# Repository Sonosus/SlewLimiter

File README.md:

# Slew Limiter
A Kosmo format slew limiter. Not tested, but it is very simple and probably works.
No panel is provided - I use custom wooden panels. I can design one though, if folks want. Send me an email or make an issue if you do.

# Attribution
This is a dual PCB of the circuit [here](http://synovatron.blogspot.com/p/diy-ideas.html). All credit to the original author.

[![CC BY-SA 4.0][cc-by-sa-shield]][cc-by-sa]

This work is licensed under a
[Creative Commons Attribution-ShareAlike 4.0 International License][cc-by-sa].

[![CC BY-SA 4.0][cc-by-sa-image]][cc-by-sa]

[cc-by-sa]: http://creativecommons.org/licenses/by-sa/4.0/
[cc-by-sa-image]: https://licensebuttons.net/l/by-sa/4.0/88x31.png
[cc-by-sa-shield]: https://img.shields.io/badge/License-CC%20BY--SA%204.0-lightgrey.svg

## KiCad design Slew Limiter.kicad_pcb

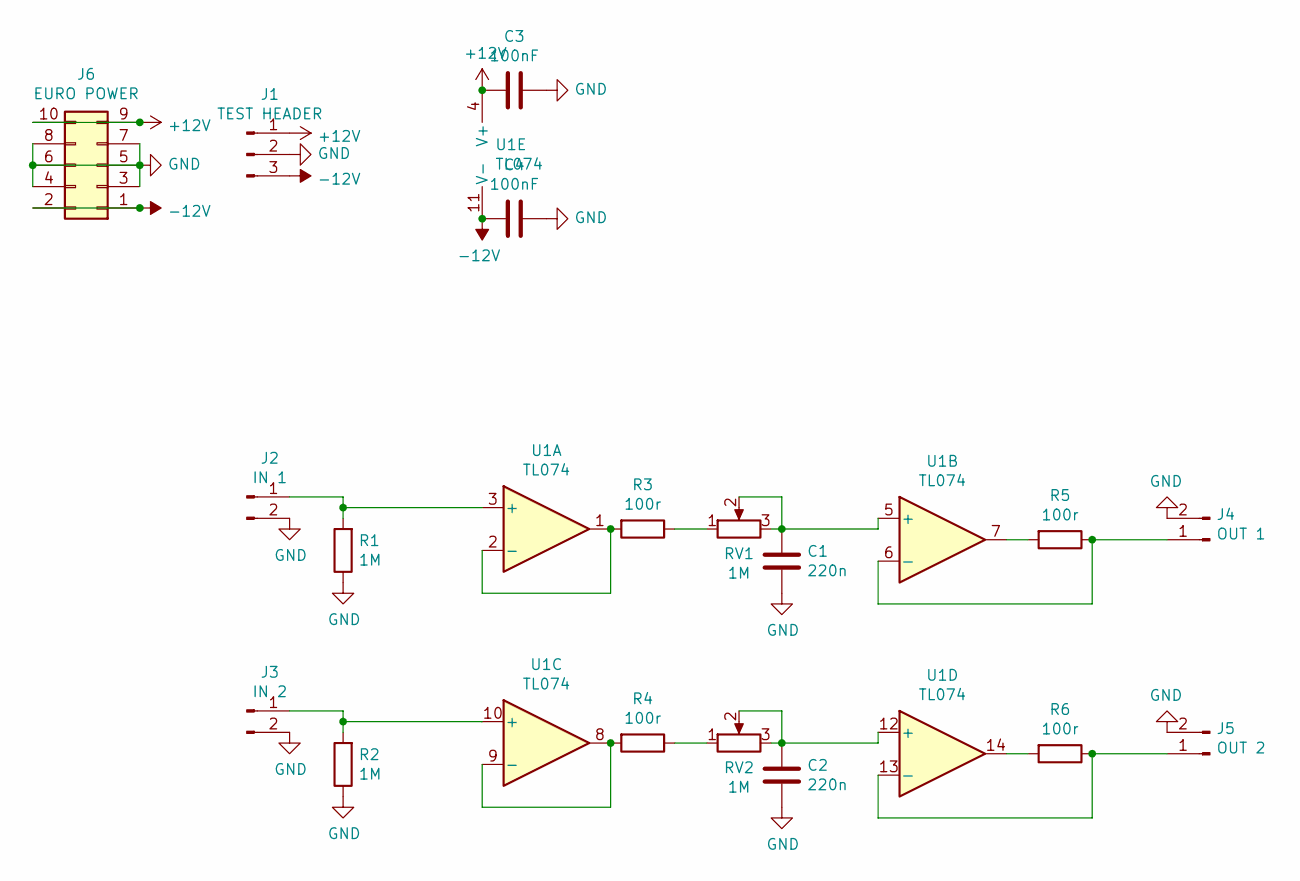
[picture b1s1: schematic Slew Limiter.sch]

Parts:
C1, C2: 220n; C_Disc_D4.3mm_W1.9mm_P5.00mm
C3, C4: 100nF; C_Disc_D6.0mm_W4.4mm_P5.00mm
J1: TEST HEADER; PinHeader_1x03_P2.54mm_Vertical
J2: IN 1; PinHeader_1x02_P2.54mm_Vertical
J3: IN 2; PinHeader_1x02_P2.54mm_Vertical
J4: OUT 1; PinHeader_1x02_P2.54mm_Vertical
J5: OUT 2; PinHeader_1x02_P2.54mm_Vertical
J6: EURO POWER; PinHeader_2x05_P2.54mm_Vertical
R1, R2: 1M; R_Axial_DIN0207_L6.3mm_D2.5mm_P7.62mm_Horizontal
R3, R4, R5, R6: 100r; R_Axial_DIN0207_L6.3mm_D2.5mm_P7.62mm_Horizontal
RV1, RV2: 1M; Alpha_16mm_PCBMount
U1: TL074; DIP-14_W7.62mm_Socket_LongPads

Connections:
+12V: C3.2, J1.1, J6.9, J6.10, U1.4 (V+)
-12V: C4.2, J1.3, J6.1, J6.2, U1.11 (V-)
GND: C1.2, C2.2, C3.1, C4.1, J1.2, J2.2, J3.2, J4.2, J5.2, J6.3, J6.4, J6.5, J6.6, J6.7, J6.8, R1.1, R2.1
unnamed: C1.1, RV1.2, RV1.3, U1.5 (+)
unnamed: C2.1, RV2.2, RV2.3, U1.12 (+)
unnamed: J2.1, R1.2, U1.3 (+)
unnamed: J3.1, R2.2, U1.10 (+)
unnamed: J4.1, R5.1, U1.6 (-)
unnamed: J5.1, R6.1, U1.13 (-)
unnamed: R3.1, RV1.1
unnamed: R3.2, U1.1, U1.2 (-)
unnamed: R4.1, RV2.1
unnamed: R4.2, U1.8, U1.9 (-)
unnamed: R5.2, U1.7
unnamed: R6.2, U1.14

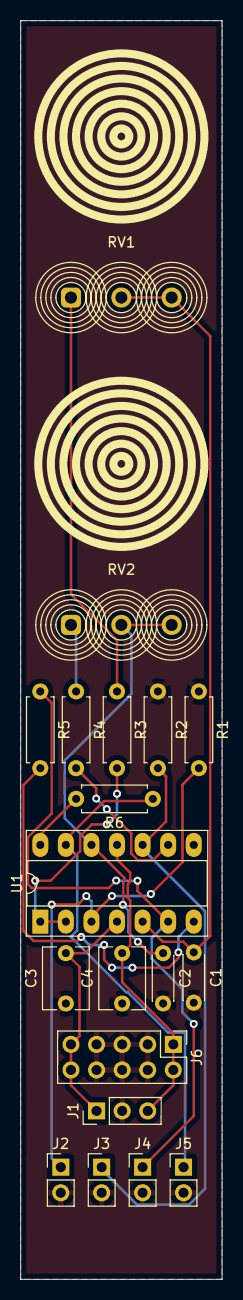
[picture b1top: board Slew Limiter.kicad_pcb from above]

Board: 2 copper layers, 20.0 x 125.0 mm, 19 parts (0 on the bottom side), 15 nets.

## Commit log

2021-05-23 Add files and rendering
2021-05-23 Add schematic
2021-05-23 Add image to readme
2021-05-23 Add attribution
2021-05-24 [ImgBot] Optimize images
    /SlewLimRender.png -- 147.32kb -> 135.50kb (8.02%)
